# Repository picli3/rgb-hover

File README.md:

# rgb-hover

Controlador para cinta o carga **RGB** basado en MOSFETs de potencia, pensado para conmutación y manejo práctico de iluminación multicolor.

## Propósito del proyecto
Este diseño busca facilitar el control de canales RGB mediante una PCB simple y robusta, adecuada para efectos visuales, tiras LED o sistemas decorativos con cargas relativamente altas.

## Qué incluye
- esquemático del controlador RGB
- PCB en KiCad
- documentación exportada para fabricación y montaje

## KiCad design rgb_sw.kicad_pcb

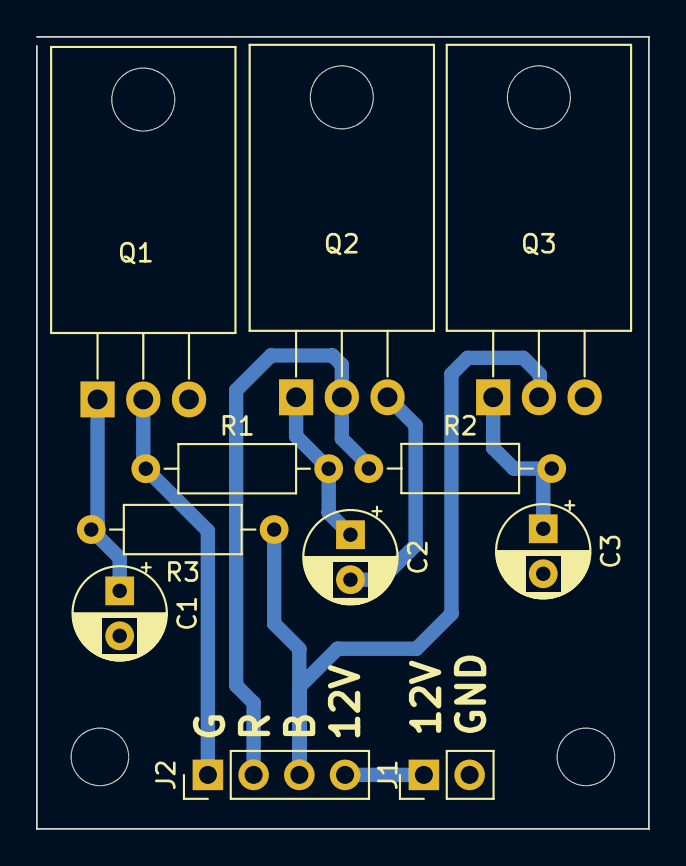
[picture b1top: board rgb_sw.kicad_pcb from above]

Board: 2 copper layers, 34.0 x 44.0 mm, 13 parts (0 on the bottom side), 8 nets.

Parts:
C1, C2, C3: 2.2uF; CP_Radial_D5.0mm_P2.50mm
H1, H3: MH; MountingHole_3.2mm_M3
J1: POWER; PinHeader_1x02_P2.54mm_Vertical
J2: RGB_TAPE; PinHeader_1x04_P2.54mm_Vertical
Q1, Q2, Q3: IRFZ44N; TO-220-3_Horizontal_TabDown
R1, R2, R3: 1M; R_Axial_DIN0207_L6.3mm_D2.5mm_P10.16mm_Horizontal

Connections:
/12V: J1.1, J2.4
/B: J2.3, Q3.2 (D), R3.1
/G: J2.1, Q1.2 (D), R1.1
/R: J2.2, Q2.2 (D), R2.1
GND: C1.2, C2.2, C3.2, J1.2, Q1.3 (S), Q2.3 (S), Q3.3 (S)
unnamed: C1.1, Q1.1 (G), R3.2
unnamed: C2.1, Q2.1 (G), R1.2
unnamed: C3.1, Q3.1 (G), R2.2

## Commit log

2023-02-23 terminando circuito
2024-09-08 actualizando a kicad 8
2026-04-29 Agrega README con descripción inicial del proyecto
2026-04-29 Mejora README con descripción específica del proyecto
